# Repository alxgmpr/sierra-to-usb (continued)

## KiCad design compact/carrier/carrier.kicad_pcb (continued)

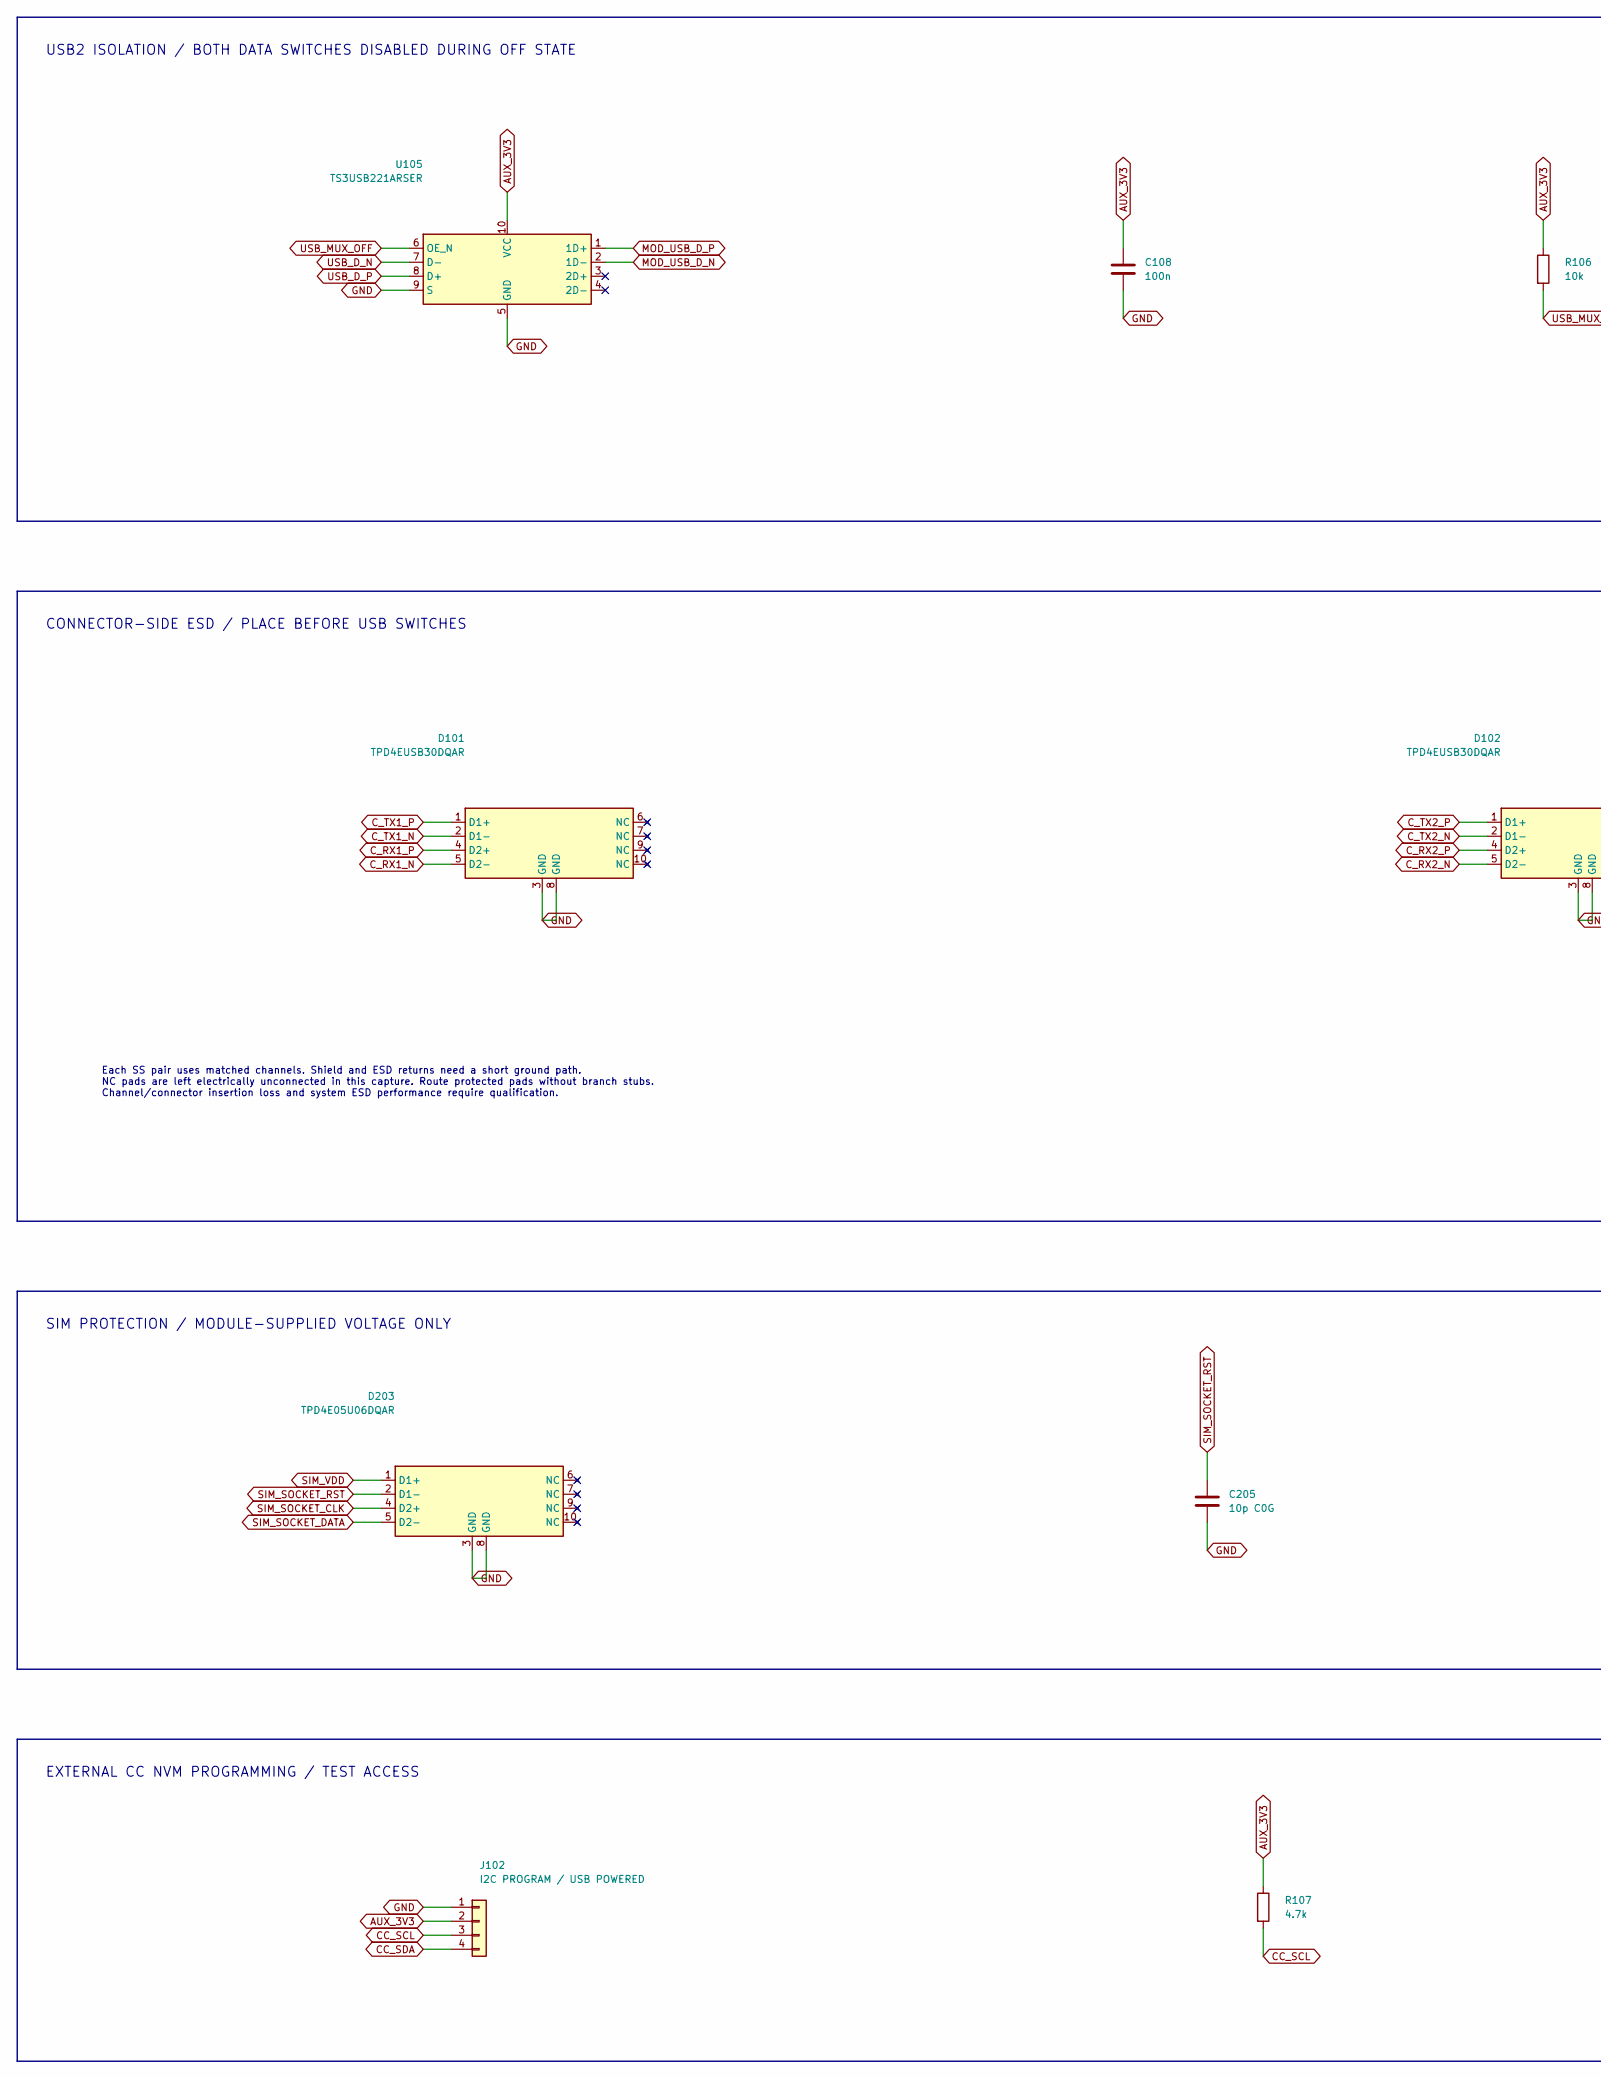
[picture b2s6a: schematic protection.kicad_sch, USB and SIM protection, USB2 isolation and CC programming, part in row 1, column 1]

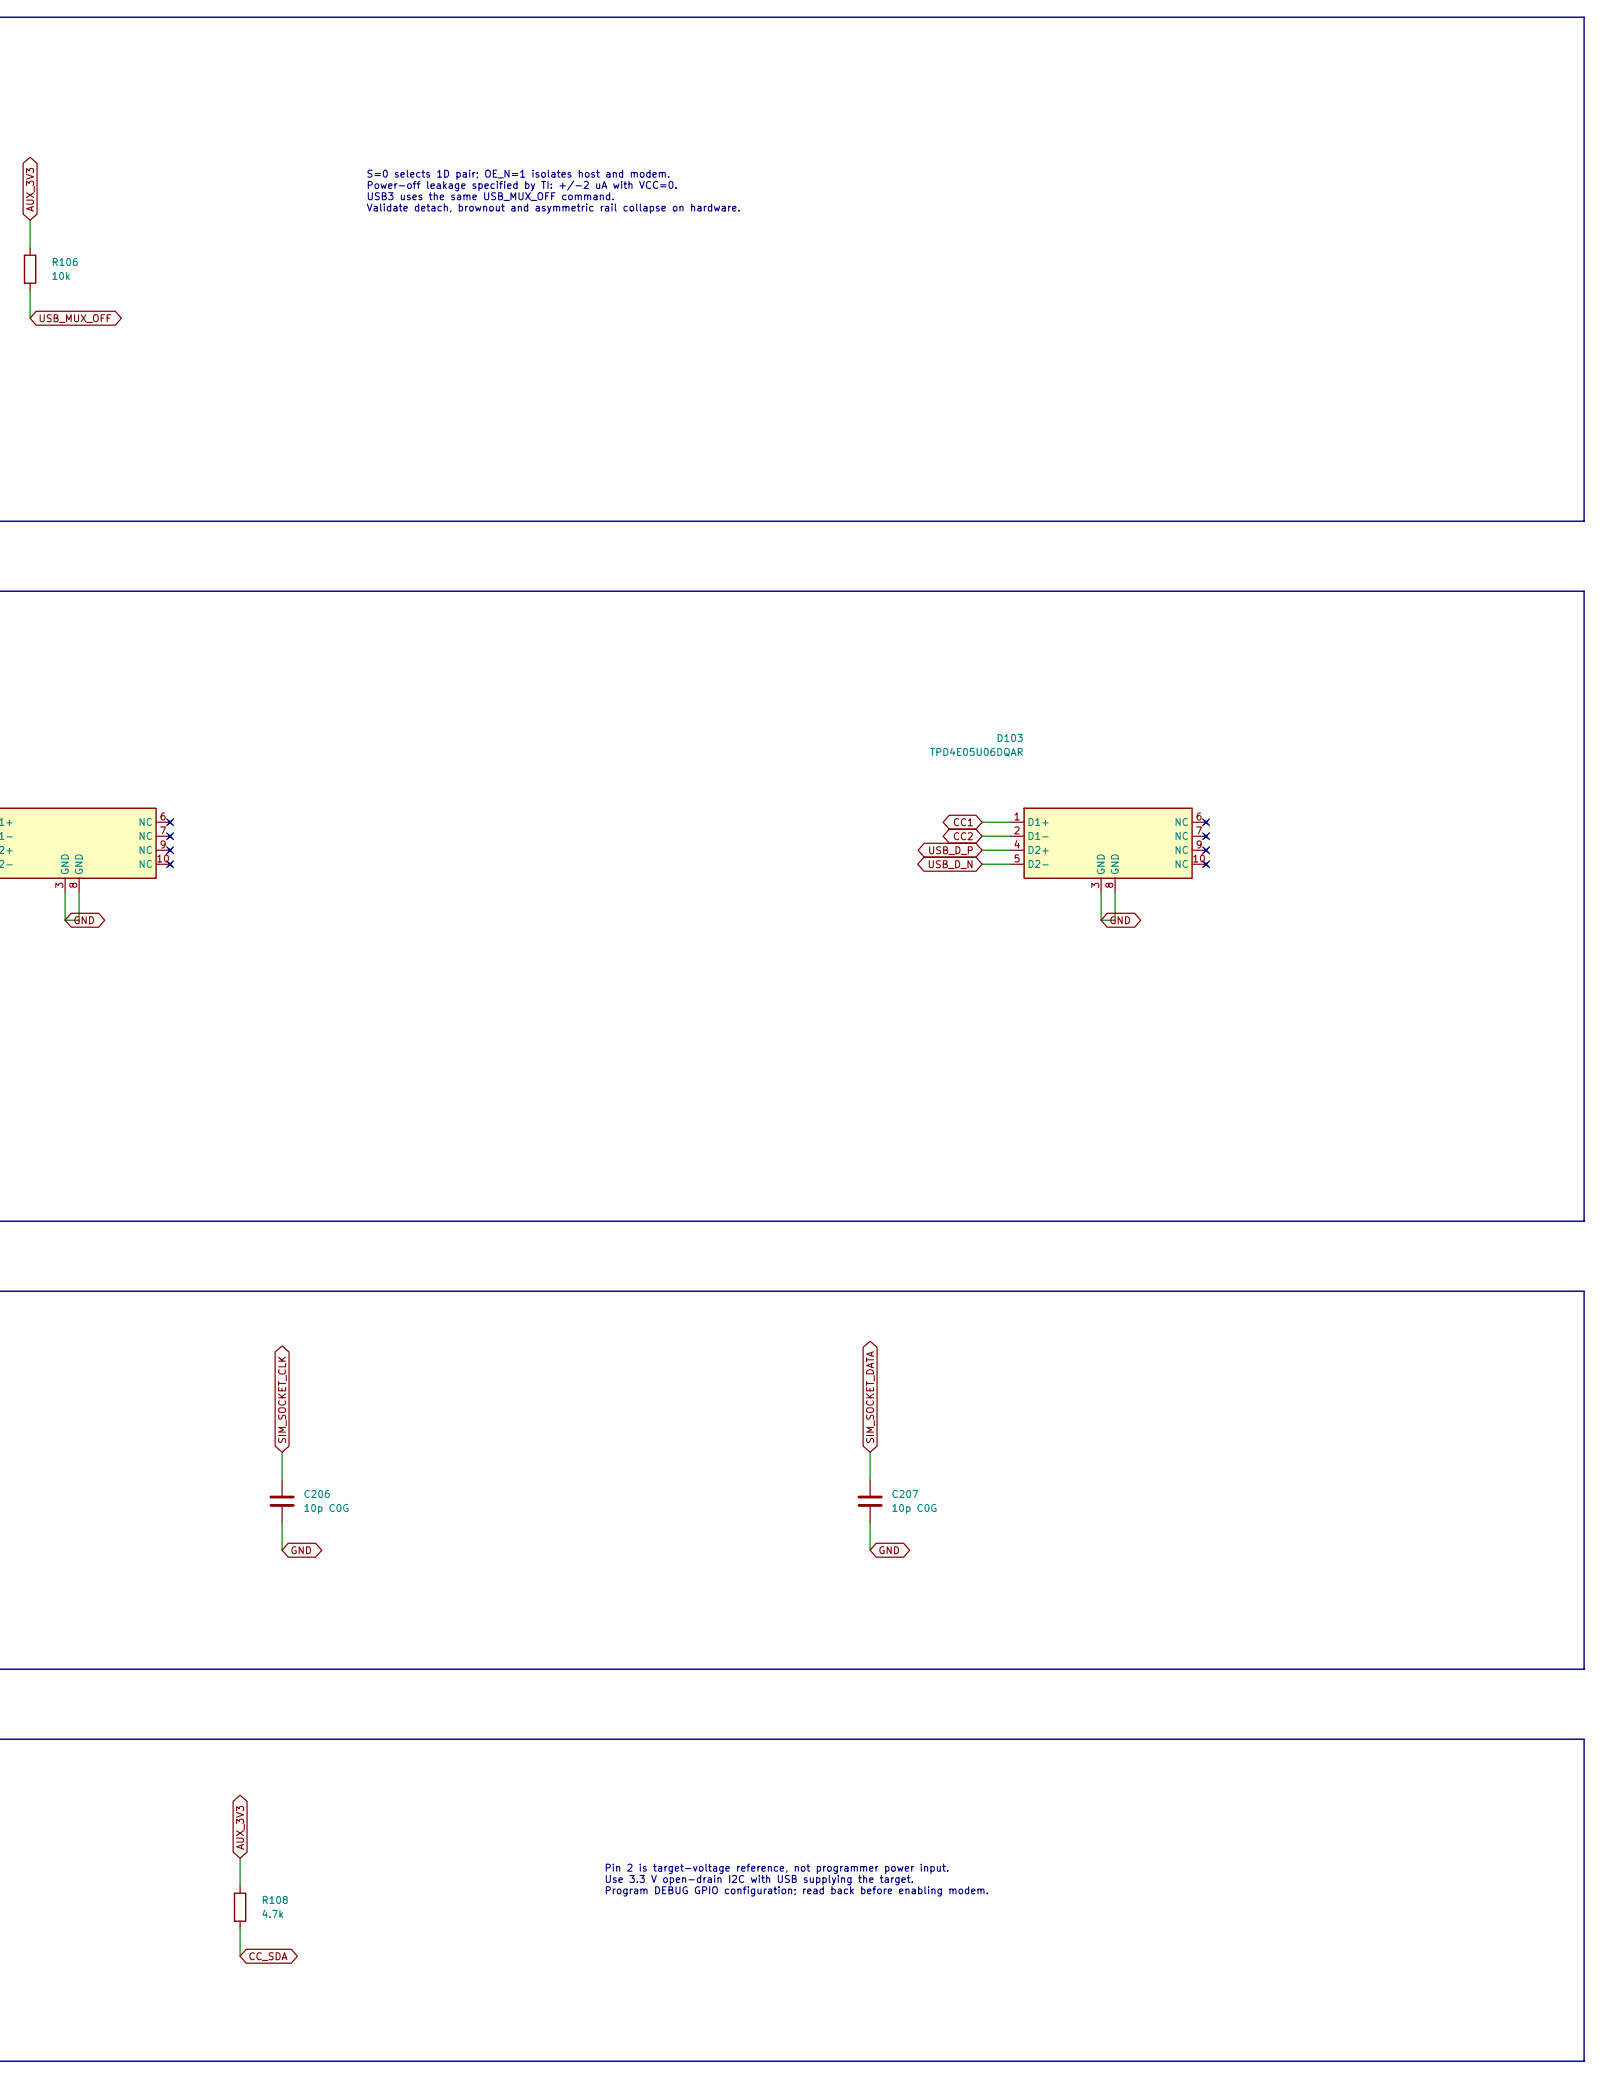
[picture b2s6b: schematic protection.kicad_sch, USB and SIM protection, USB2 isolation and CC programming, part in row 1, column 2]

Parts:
C108: 100n; C_0805_2012Metric; MPN C2012X7R1H104K085AA
C205, C206, C207: 10p C0G; C_0805_2012Metric; MPN C0805C100J5GACTU
D101, D102: TPD4EUSB30DQAR; USON-10_2.5x1.0mm_P0.5mm; MPN TPD4EUSB30DQAR
D103, D203: TPD4E05U06DQAR; USON-10_2.5x1.0mm_P0.5mm; MPN TPD4E05U06DQAR
J102: I2C PROGRAM / USB POWERED; PinHeader_1x04_P2.54mm_Vertical; MPN TSW-104-07-G-S
R106: 10k; R_0603_1608Metric; MPN RC0603FR-0710KL
R107, R108: 4.7k; R_0603_1608Metric; MPN RC0603FR-074K7L
U105: TS3USB221ARSER; Texas_UQFN-10_1.5x2mm_P0.5mm; MPN TS3USB221ARSER

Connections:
AUX_3V3: C108.1, J102.2, R106.1, R107.1, R108.1, U105.10 (VCC); also elsewhere on the board
CC1: D103.1 (D1+); also elsewhere on the board
CC2: D103.2 (D1-); also elsewhere on the board
CC_SCL: J102.3, R107.2; also elsewhere on the board
CC_SDA: J102.4, R108.2; also elsewhere on the board
C_RX1_N: D101.5 (D2-); also elsewhere on the board
C_RX1_P: D101.4 (D2+); also elsewhere on the board
C_RX2_N: D102.5 (D2-); also elsewhere on the board
C_RX2_P: D102.4 (D2+); also elsewhere on the board
C_TX1_N: D101.2 (D1-); also elsewhere on the board
C_TX1_P: D101.1 (D1+); also elsewhere on the board
C_TX2_N: D102.2 (D1-); also elsewhere on the board
C_TX2_P: D102.1 (D1+); also elsewhere on the board
GND: C108.2, C205.2, C206.2, C207.2, D101.3 (GND), D101.8 (GND), D102.3 (GND), D102.8 (GND), D103.3 (GND), D103.8 (GND), D203.3 (GND), D203.8 (GND), J102.1, U105.5 (GND), U105.9 (S); also elsewhere on the board
MOD_USB_D_N: U105.2 (1D-); also elsewhere on the board
MOD_USB_D_P: U105.1 (1D+); also elsewhere on the board
SIM_SOCKET_CLK: C206.1, D203.4 (D2+); also elsewhere on the board
SIM_SOCKET_DATA: C207.1, D203.5 (D2-); also elsewhere on the board
SIM_SOCKET_RST: C205.1, D203.2 (D1-); also elsewhere on the board
SIM_VDD: D203.1 (D1+); also elsewhere on the board
USB_D_N: D103.5 (D2-), U105.7 (D-); also elsewhere on the board
USB_D_P: D103.4 (D2+), U105.8 (D+); also elsewhere on the board
USB_MUX_OFF: R106.2, U105.6 (OE_N); also elsewhere on the board

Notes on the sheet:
USB2 ISOLATION / BOTH DATA SWITCHES DISABLED DURING OFF STATE
S=0 selects 1D pair; OE_N=1 isolates host and modem. Power-off leakage specified by TI: +/-2 uA with VCC=0. USB3 uses the same USB_MUX_OFF command. Validate detach, brownout and asymmetric rail collapse on hardware.
CONNECTOR-SIDE ESD / PLACE BEFORE USB SWITCHES
Each SS pair uses matched channels. Shield and ESD returns need a short ground path. NC pads are left electrically unconnected in this capture. Route protected pads without branch stubs. Channel/connector insertion loss and system ESD performance require qualification.
SIM PROTECTION / MODULE-SUPPLIED VOLTAGE ONLY
EXTERNAL CC NVM PROGRAMMING / TEST ACCESS
Pin 2 is target-voltage reference, not programmer power input. Use 3.3 V open-drain I2C with USB supplying the target. Program DEBUG GPIO configuration; read back before enabling modem.

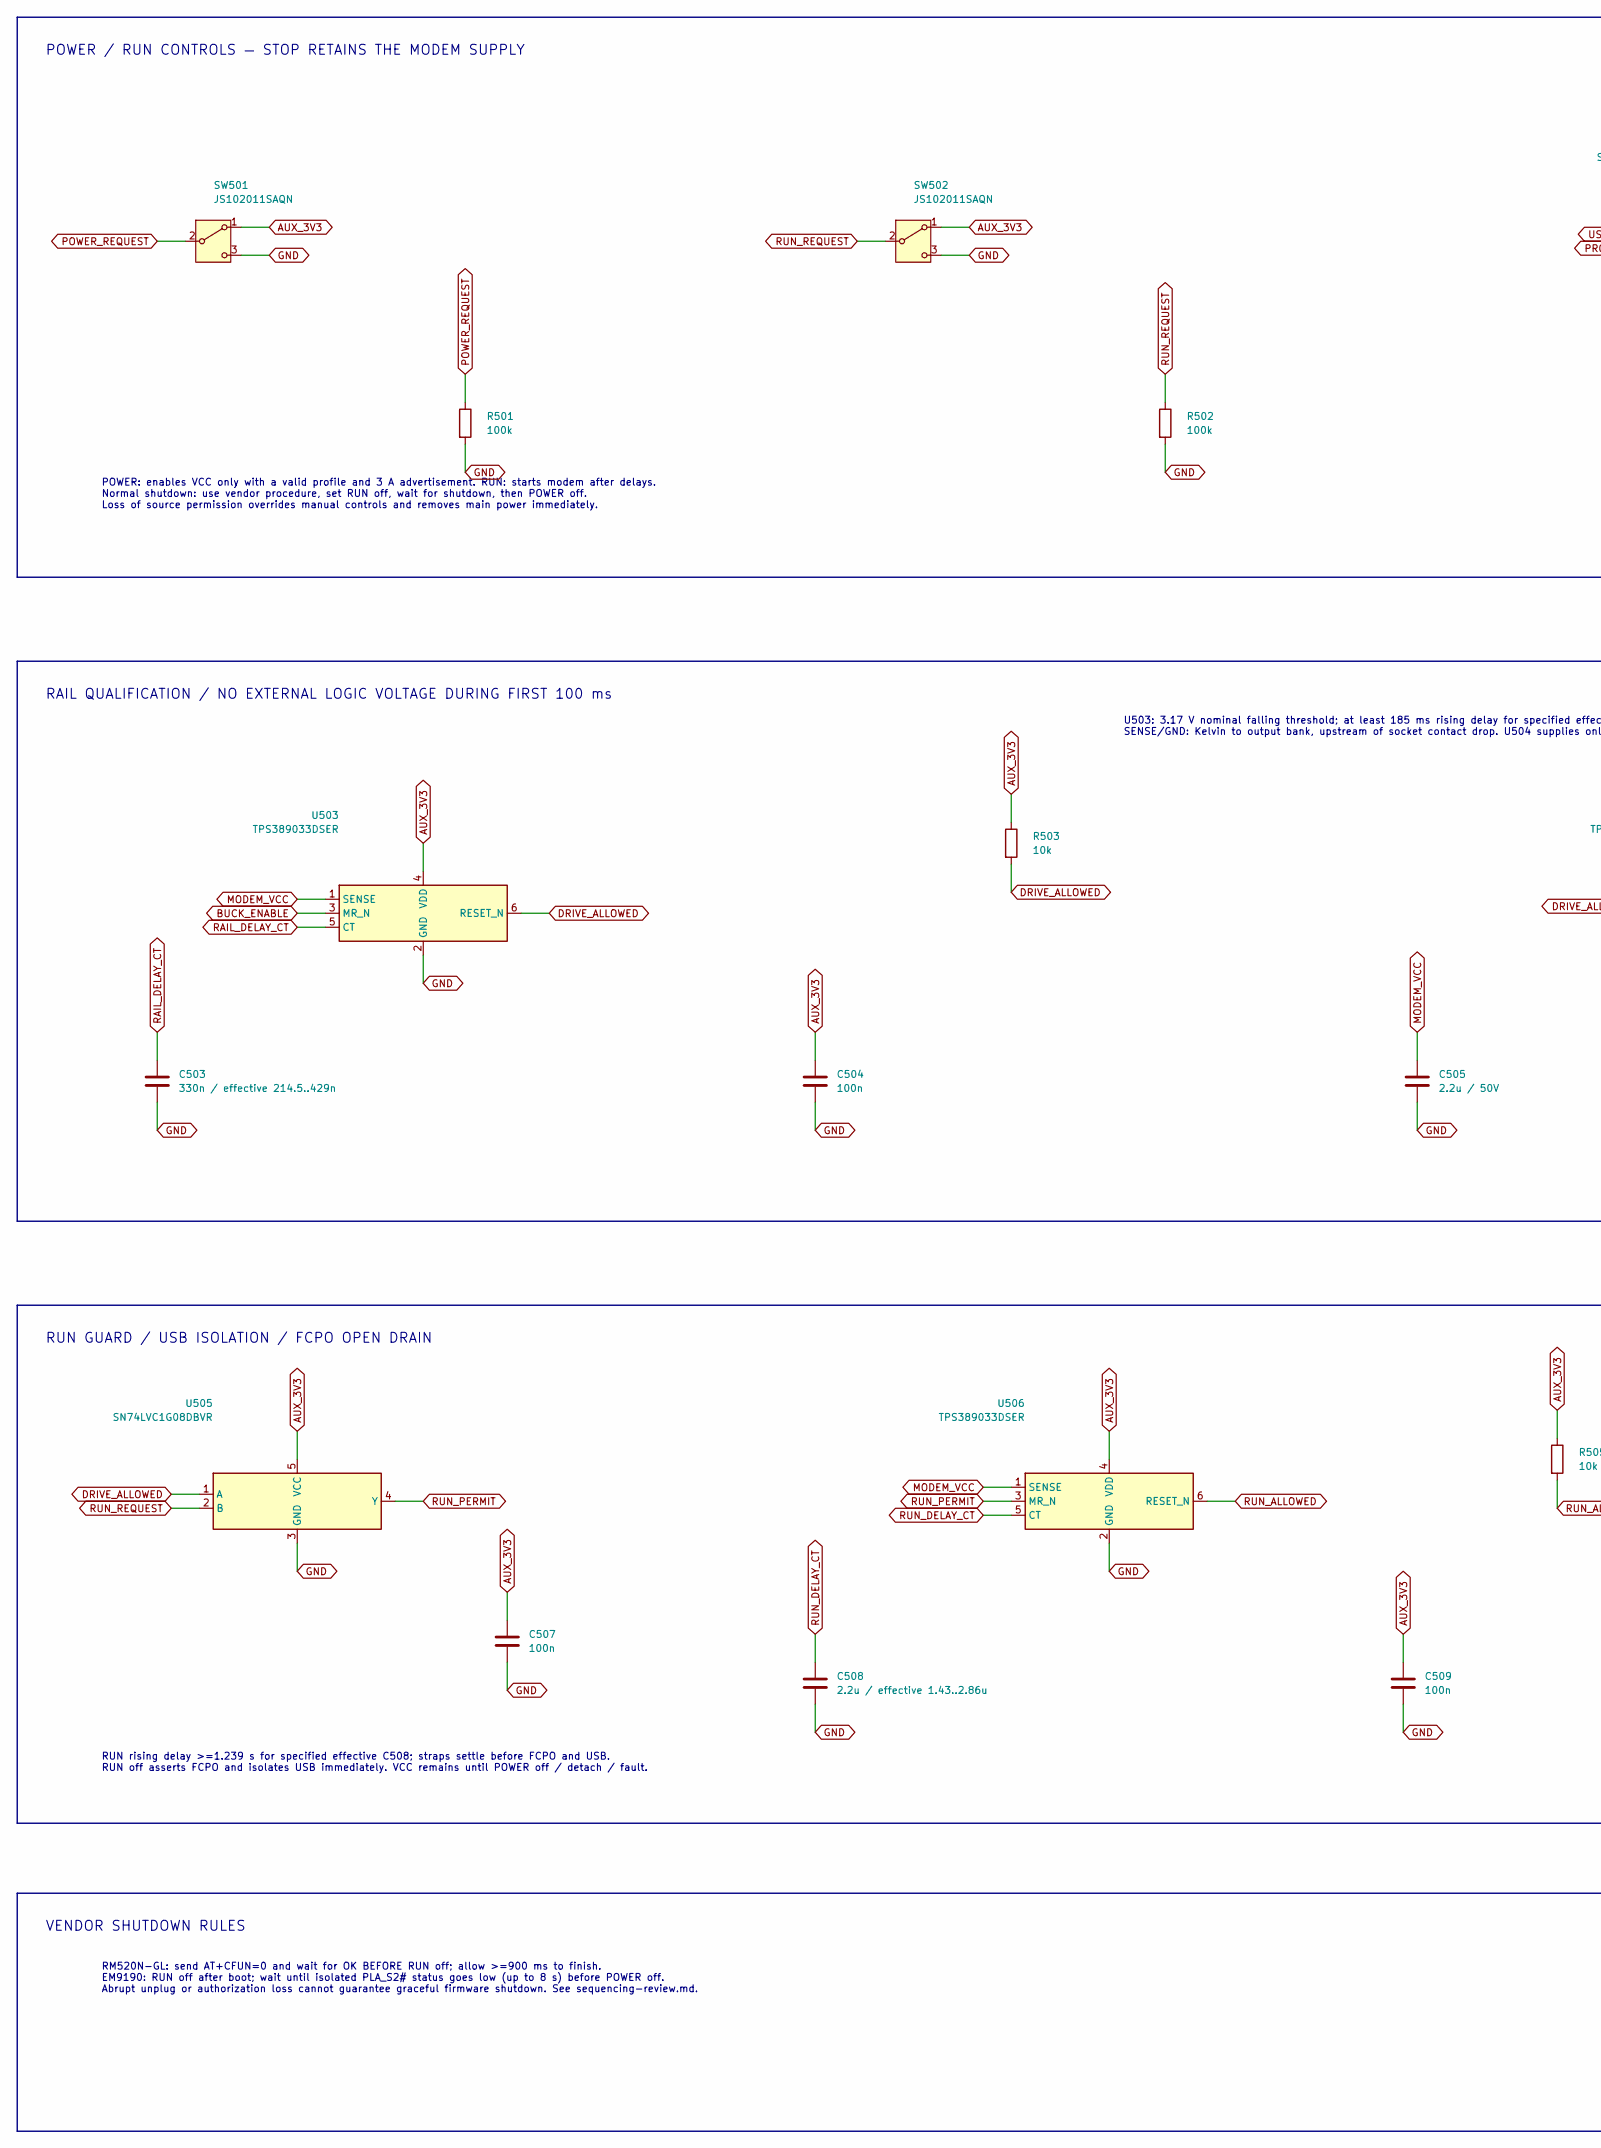
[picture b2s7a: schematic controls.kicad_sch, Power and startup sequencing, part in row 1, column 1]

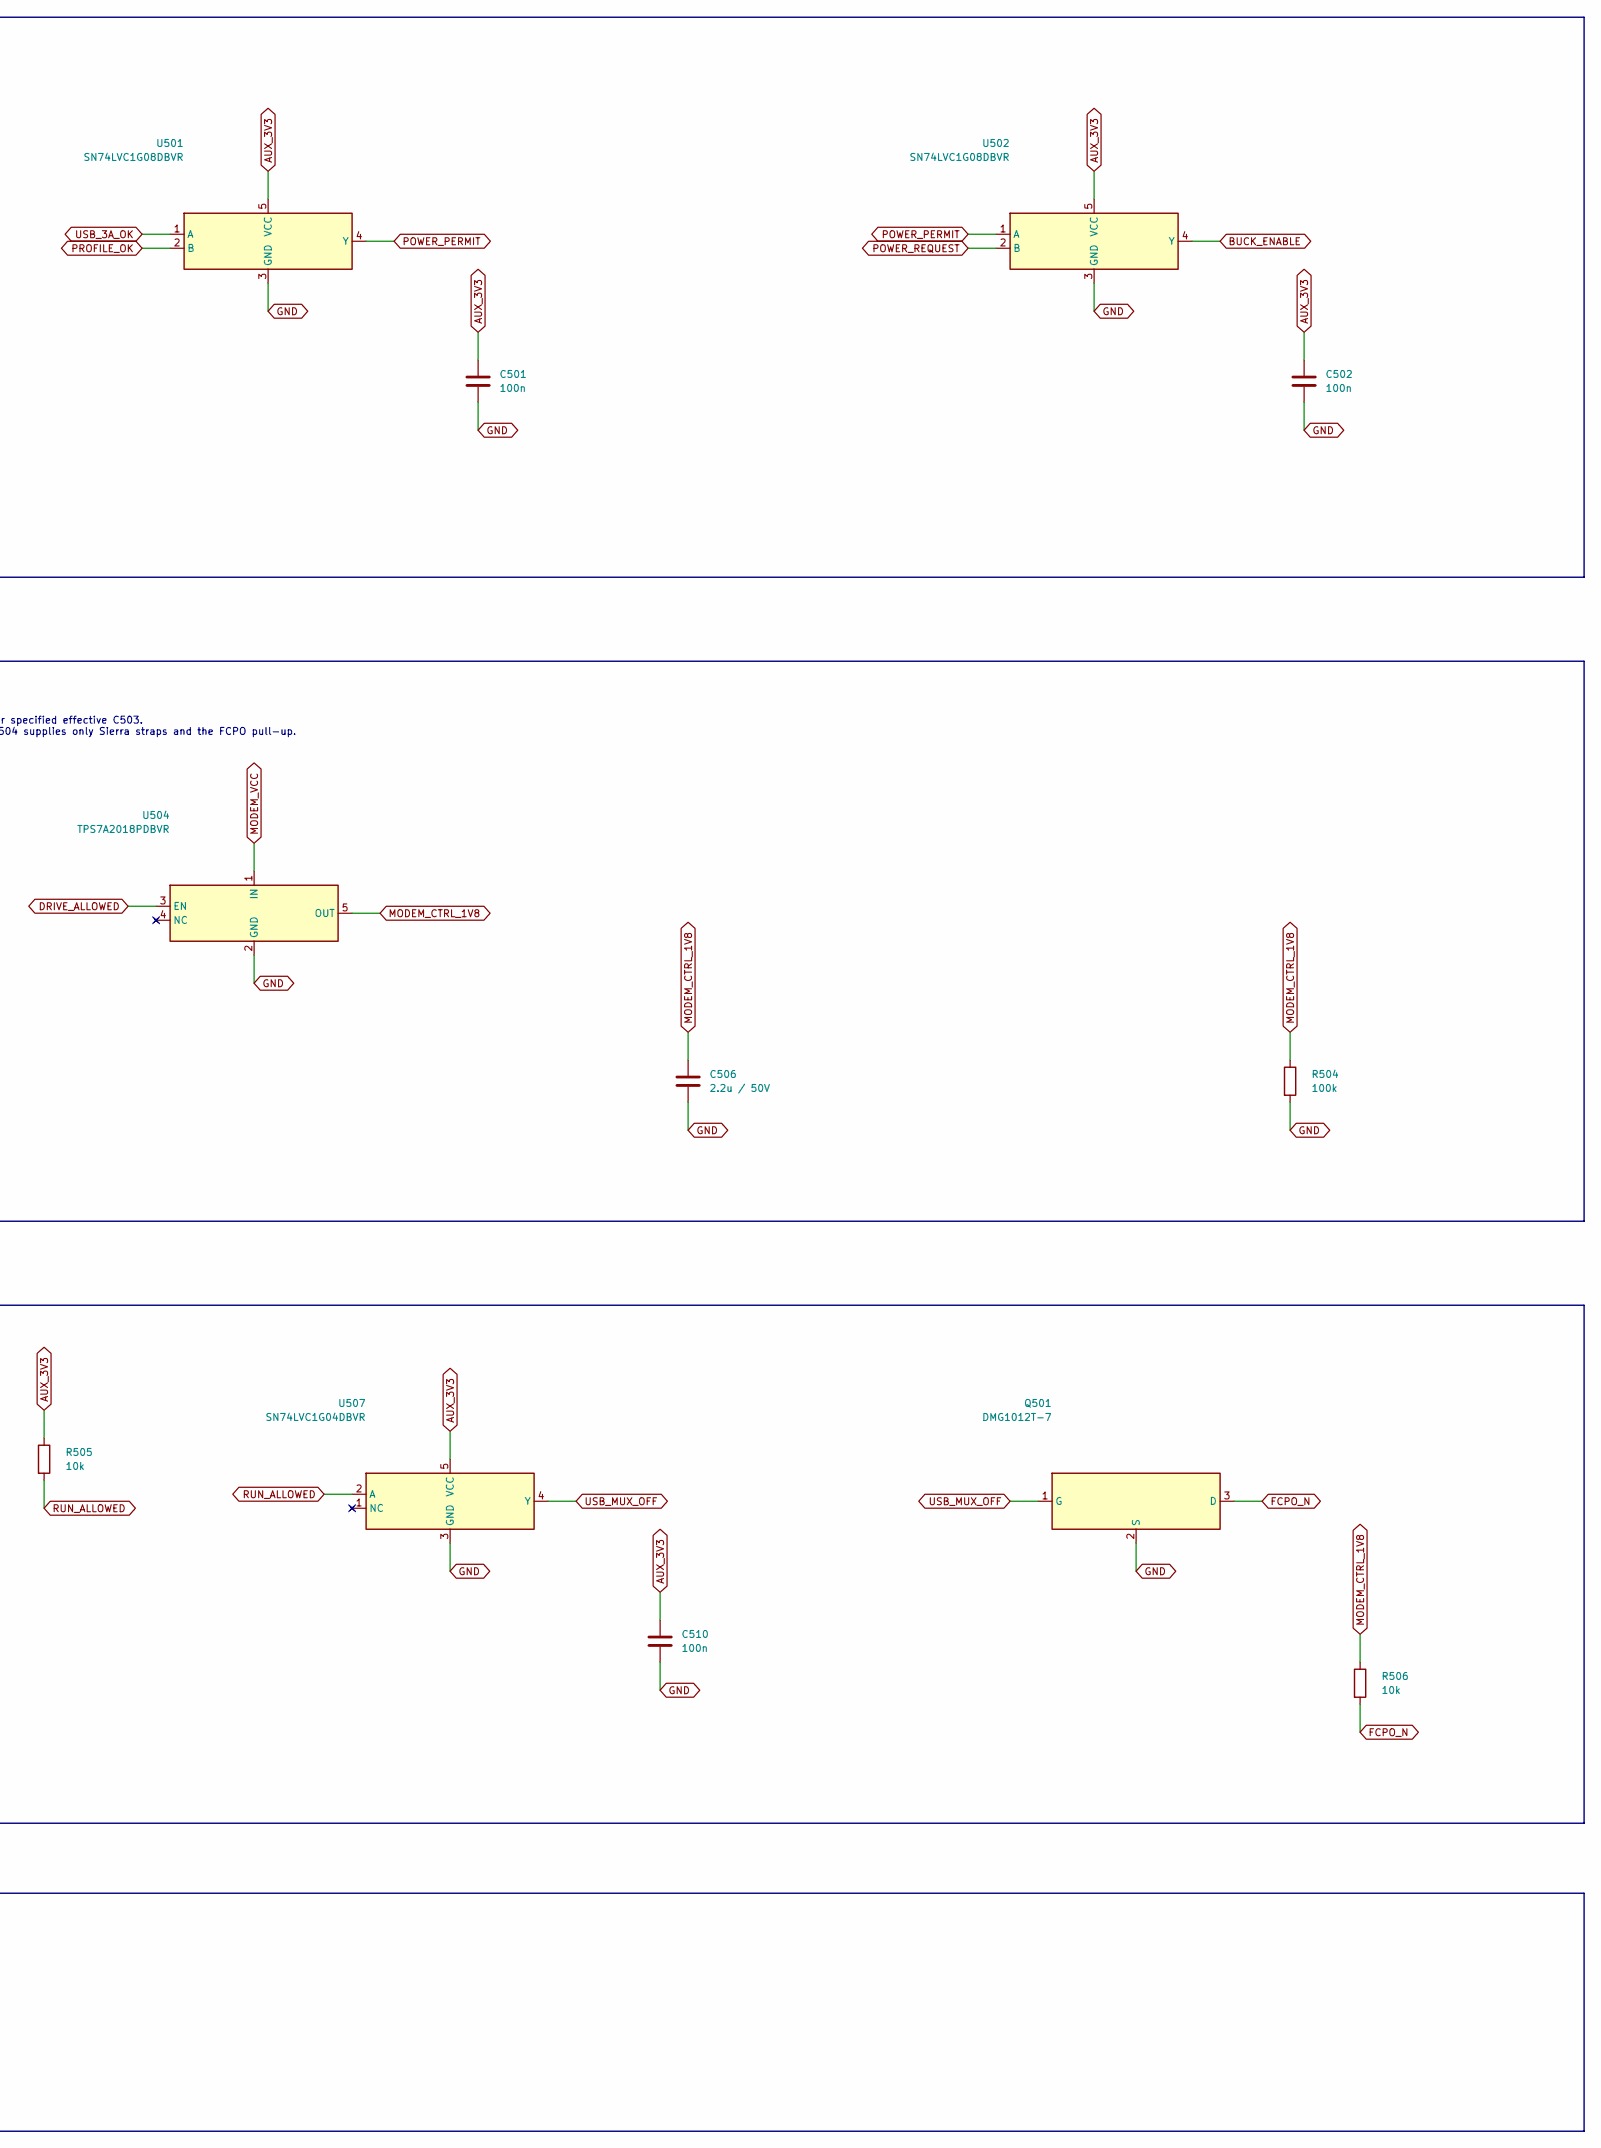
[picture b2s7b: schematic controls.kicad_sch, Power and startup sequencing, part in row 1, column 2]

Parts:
C501, C502, C504, C507, C509, C510: 100n; C_0805_2012Metric; MPN C2012X7R1H104K085AA
C503: 330n / effective 214.5..429n; C_0805_2012Metric; MPN C2012X7R1H334K125AA
C505, C506: 2.2u / 50V; C_1206_3216Metric; MPN C3216X7R1H225K160AB
C508: 2.2u / effective 1.43..2.86u; C_1206_3216Metric; MPN C3216X7R1H225K160AB
Q501: DMG1012T-7; SOT-523; MPN DMG1012T-7
R501, R502, R504: 100k; R_0603_1608Metric; MPN RC0603FR-07100KL
R503, R505, R506: 10k; R_0603_1608Metric; MPN RC0603FR-0710KL
SW501, SW502: JS102011SAQN; SW_SPDT_CK_JS102011SAQN; MPN JS102011SAQN
U501, U502, U505: SN74LVC1G08DBVR; SOT-23-5; MPN SN74LVC1G08DBVR
U503, U506: TPS389033DSER; WSON-6_1.5x1.5mm_P0.5mm; MPN TPS389033DSER
U504: TPS7A2018PDBVR; SOT-23-5; MPN TPS7A2018PDBVR
U507: SN74LVC1G04DBVR; SOT-23-5; MPN SN74LVC1G04DBVR

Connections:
AUX_3V3: C501.1, C502.1, C504.1, C507.1, C509.1, C510.1, R503.1, R505.1, SW501.1 (A), SW502.1 (A), U501.5 (VCC), U502.5 (VCC), U503.4 (VDD), U505.5 (VCC), U506.4 (VDD), U507.5 (VCC); also elsewhere on the board
BUCK_ENABLE: U502.4 (Y), U503.3 (MR_N); also elsewhere on the board
DRIVE_ALLOWED: R503.2, U503.6 (RESET_N), U504.3 (EN), U505.1 (A); also elsewhere on the board
FCPO_N: Q501.3 (D), R506.2; also elsewhere on the board
GND: C501.2, C502.2, C503.2, C504.2, C505.2, C506.2, C507.2, C508.2, C509.2, C510.2, Q501.2 (S), R501.2, R502.2, R504.2, SW501.3 (C), SW502.3 (C), U501.3 (GND), U502.3 (GND), U503.2 (GND), U504.2 (GND), U505.3 (GND), U506.2 (GND), U507.3 (GND); also elsewhere on the board
MODEM_CTRL_1V8: C506.1, R504.1, R506.1, U504.5 (OUT); also elsewhere on the board
MODEM_VCC: C505.1, U503.1 (SENSE), U504.1 (IN), U506.1 (SENSE); also elsewhere on the board
POWER_PERMIT: U501.4 (Y), U502.1 (A)
POWER_REQUEST: R501.1, SW501.2 (B), U502.2 (B)
PROFILE_OK: U501.2 (B); also elsewhere on the board
RAIL_DELAY_CT: C503.1, U503.5 (CT)
RUN_ALLOWED: R505.2, U506.6 (RESET_N), U507.2 (A); also elsewhere on the board
RUN_DELAY_CT: C508.1, U506.5 (CT)
RUN_PERMIT: U505.4 (Y), U506.3 (MR_N)
RUN_REQUEST: R502.1, SW502.2 (B), U505.2 (B)
USB_3A_OK: U501.1 (A); also elsewhere on the board
USB_MUX_OFF: Q501.1 (G), U507.4 (Y); also elsewhere on the board

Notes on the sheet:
POWER / RUN CONTROLS — STOP RETAINS THE MODEM SUPPLY
POWER: enables VCC only with a valid profile and 3 A advertisement. RUN: starts modem after delays. Normal shutdown: use vendor procedure, set RUN off, wait for shutdown, then POWER off. Loss of source permission overrides manual controls and removes main power immediately.
RAIL QUALIFICATION / NO EXTERNAL LOGIC VOLTAGE DURING FIRST 100 ms
U503: 3.17 V nominal falling threshold; at least 185 ms rising delay for specified effective C503. SENSE/GND: Kelvin to output bank, upstream of socket contact drop. U504 supplies only Sierra straps and the FCPO pull-up.
RUN GUARD / USB ISOLATION / FCPO OPEN DRAIN
RUN rising delay >=1.239 s for specified effective C508; straps settle before FCPO and USB. RUN off asserts FCPO and isolates USB immediately. VCC remains until POWER off / detach / fault.
VENDOR SHUTDOWN RULES
RM520N-GL: send AT+CFUN=0 and wait for OK BEFORE RUN off; allow >=900 ms to finish. EM9190: RUN off after boot; wait until isolated PLA_S2# status goes low (up to 8 s) before POWER off. Abrupt unplug or authorization loss cannot guarantee graceful firmware shutdown. See sequencing-review.md.
